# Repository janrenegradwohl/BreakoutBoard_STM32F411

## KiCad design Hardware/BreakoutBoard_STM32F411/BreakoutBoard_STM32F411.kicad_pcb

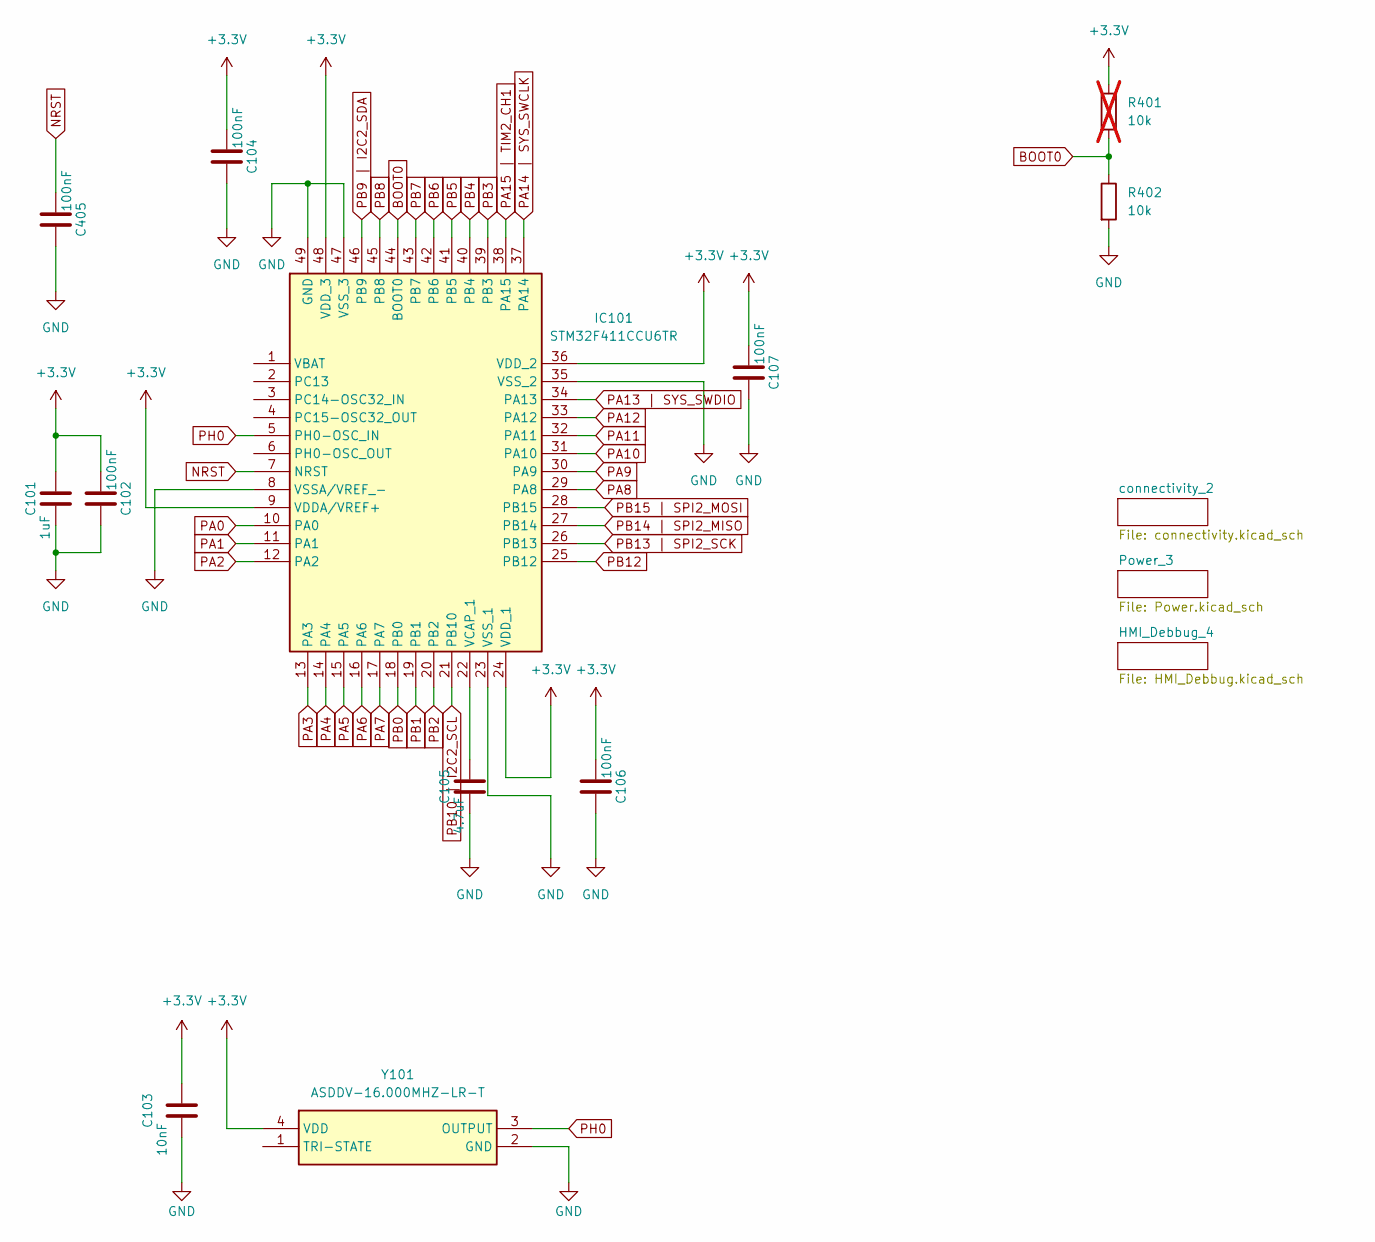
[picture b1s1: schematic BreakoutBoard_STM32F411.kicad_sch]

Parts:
C101: 1uF; C_0603_1608Metric
C102, C104, C106, C107, C405: 100nF; C_0402_1005Metric
C103: 10nF; C_0402_1005Metric
C105: 4.7uF; C_0805_2012Metric
IC101: STM32F411CCU6TR; QFN50P700X700X65-49N-D; Mouser Part Number 511-STM32F411CCU6TR
R401: 10k; R_0402_1005Metric; not fitted
R402: 10k; R_0402_1005Metric
Y101: ASDDV-16.000MHZ-LR-T; AbraconASDDV; Mouser Part Number 815-ASDDV-1600MHZLRT

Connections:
+3.3V: C101.2, C102.1, C103.2, C104.1, C106.1, C107.1, IC101.9 (VDDA/VREF+), IC101.24 (VDD_1), IC101.36 (VDD_2), IC101.48 (VDD_3), R401.1, Y101.4 (VDD); also elsewhere on the board
BOOT0: IC101.44 (BOOT0), R401.2, R402.1
GND: C101.1, C102.2, C103.1, C104.2, C105.1, C106.2, C107.2, C405.2, IC101.8 (VSSA/VREF_-), IC101.23 (VSS_1), IC101.35 (VSS_2), IC101.47 (VSS_3), IC101.49 (GND), R402.2, Y101.2 (GND); also elsewhere on the board
NRST: C405.1, IC101.7 (NRST)
unnamed: C105.2, IC101.22 (VCAP_1)
PA0: IC101.10 (PA0); also elsewhere on the board
PA1: IC101.11 (PA1); also elsewhere on the board
PA2: IC101.12 (PA2); also elsewhere on the board
PA3: IC101.13 (PA3); also elsewhere on the board
PA4: IC101.14 (PA4); also elsewhere on the board
PA5: IC101.15 (PA5); also elsewhere on the board
PA6: IC101.16 (PA6); also elsewhere on the board
PA7: IC101.17 (PA7); also elsewhere on the board
PA8: IC101.29 (PA8); also elsewhere on the board
PA9: IC101.30 (PA9); also elsewhere on the board
PA10: IC101.31 (PA10); also elsewhere on the board
PA11: IC101.32 (PA11); also elsewhere on the board
PA12: IC101.33 (PA12); also elsewhere on the board
PA13 | SYS_SWDIO: IC101.34 (PA13); also elsewhere on the board
PA14 | SYS_SWCLK: IC101.37 (PA14); also elsewhere on the board
PA15 | TIM2_CH1: IC101.38 (PA15); also elsewhere on the board
PB0: IC101.18 (PB0); also elsewhere on the board
PB1: IC101.19 (PB1); also elsewhere on the board
PB2: IC101.20 (PB2)
PB3: IC101.39 (PB3); also elsewhere on the board
PB4: IC101.40 (PB4); also elsewhere on the board
PB5: IC101.41 (PB5); also elsewhere on the board
PB6: IC101.42 (PB6); also elsewhere on the board
PB7: IC101.43 (PB7); also elsewhere on the board
PB8: IC101.45 (PB8); also elsewhere on the board
PB9 | I2C2_SDA: IC101.46 (PB9)
PB10 | I2C2_SCL: IC101.21 (PB10)
PB12: IC101.25 (PB12); also elsewhere on the board
PB13 | SPI2_SCK: IC101.26 (PB13); also elsewhere on the board
PB14 | SPI2_MISO: IC101.27 (PB14); also elsewhere on the board
PB15 | SPI2_MOSI: IC101.28 (PB15); also elsewhere on the board
PH0: IC101.5 (PH0-OSC_IN), Y101.3 (OUTPUT)

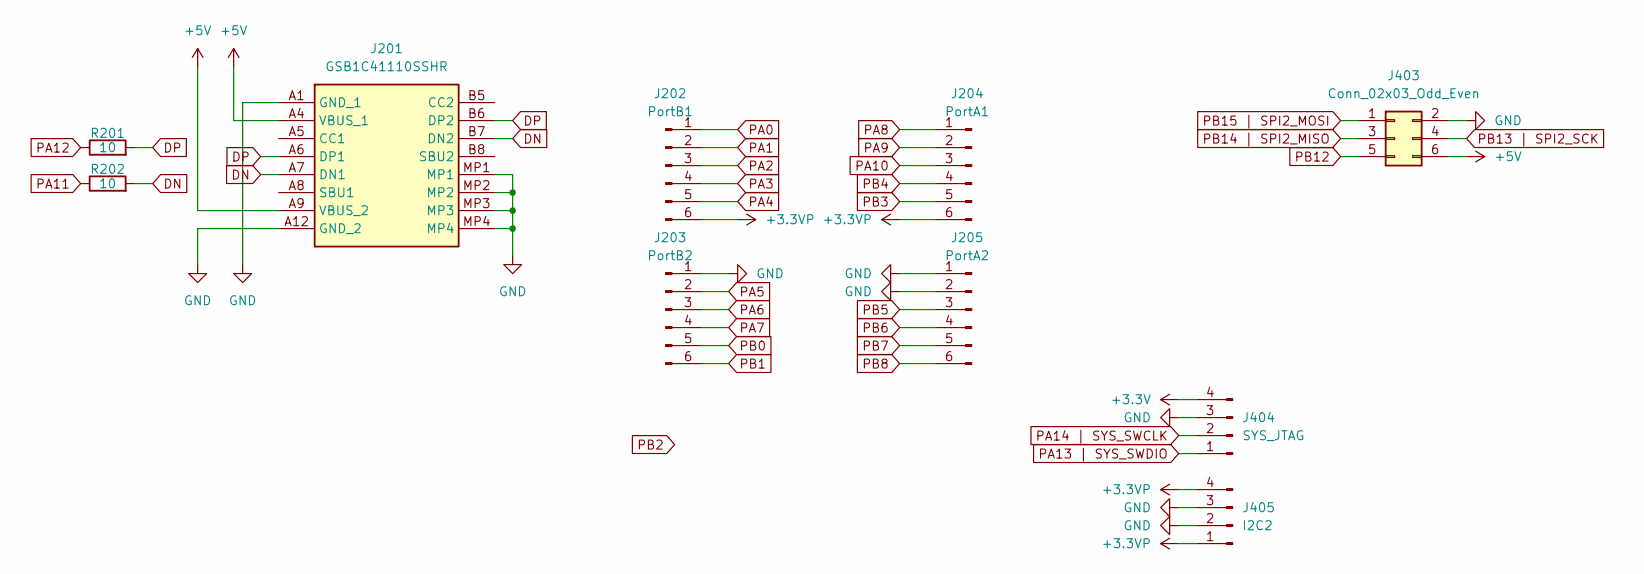
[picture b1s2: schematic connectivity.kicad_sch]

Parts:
J201: GSB1C41110SSHR; Manufacturer_Part_Number GSB1C41110SSHR
J202: PortB1; PinHeader_1x06_P2.54mm_Vertical
J203: PortB2; PinHeader_1x06_P2.54mm_Vertical
J204: PortA1; PinHeader_1x06_P2.54mm_Vertical
J205: PortA2; PinHeader_1x06_P2.54mm_Vertical
J403: Conn_02x03_Odd_Even; PinHeader_2x03_P2.54mm_Vertical
J404: SYS_JTAG; PinHeader_1x04_P2.54mm_Vertical
J405: I2C2; PinHeader_1x04_P2.54mm_Vertical
R201, R202: 10; R_0603_1608Metric

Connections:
+3.3V: J404.4; also elsewhere on the board
+3.3VP: J202.6, J204.6, J405.1, J405.4; also elsewhere on the board
+5V: J201.A4 (VBUS_1), J201.A9 (VBUS_2), J403.6; also elsewhere on the board
DN: J201.A7 (DN1), J201.B7 (DN2), R202.2
DP: J201.A6 (DP1), J201.B6 (DP2), R201.2
GND: J201.A1 (GND_1), J201.A12 (GND_2), J201.MP1, J201.MP2, J201.MP3, J201.MP4, J203.1, J205.1, J205.2, J403.2, J404.3, J405.2, J405.3; also elsewhere on the board
PA0: J202.1; also elsewhere on the board
PA1: J202.2; also elsewhere on the board
PA2: J202.3; also elsewhere on the board
PA3: J202.4; also elsewhere on the board
PA4: J202.5; also elsewhere on the board
PA5: J203.2; also elsewhere on the board
PA6: J203.3; also elsewhere on the board
PA7: J203.4; also elsewhere on the board
PA8: J204.1; also elsewhere on the board
PA9: J204.2; also elsewhere on the board
PA10: J204.3; also elsewhere on the board
PA11: R202.1; also elsewhere on the board
PA12: R201.1; also elsewhere on the board
PA13 | SYS_SWDIO: J404.1; also elsewhere on the board
PA14 | SYS_SWCLK: J404.2; also elsewhere on the board
PB0: J203.5; also elsewhere on the board
PB1: J203.6; also elsewhere on the board
PB3: J204.5; also elsewhere on the board
PB4: J204.4; also elsewhere on the board
PB5: J205.3; also elsewhere on the board
PB6: J205.4; also elsewhere on the board
PB7: J205.5; also elsewhere on the board
PB8: J205.6; also elsewhere on the board
PB12: J403.5; also elsewhere on the board
PB13 | SPI2_SCK: J403.4; also elsewhere on the board
PB14 | SPI2_MISO: J403.3; also elsewhere on the board
PB15 | SPI2_MOSI: J403.1; also elsewhere on the board

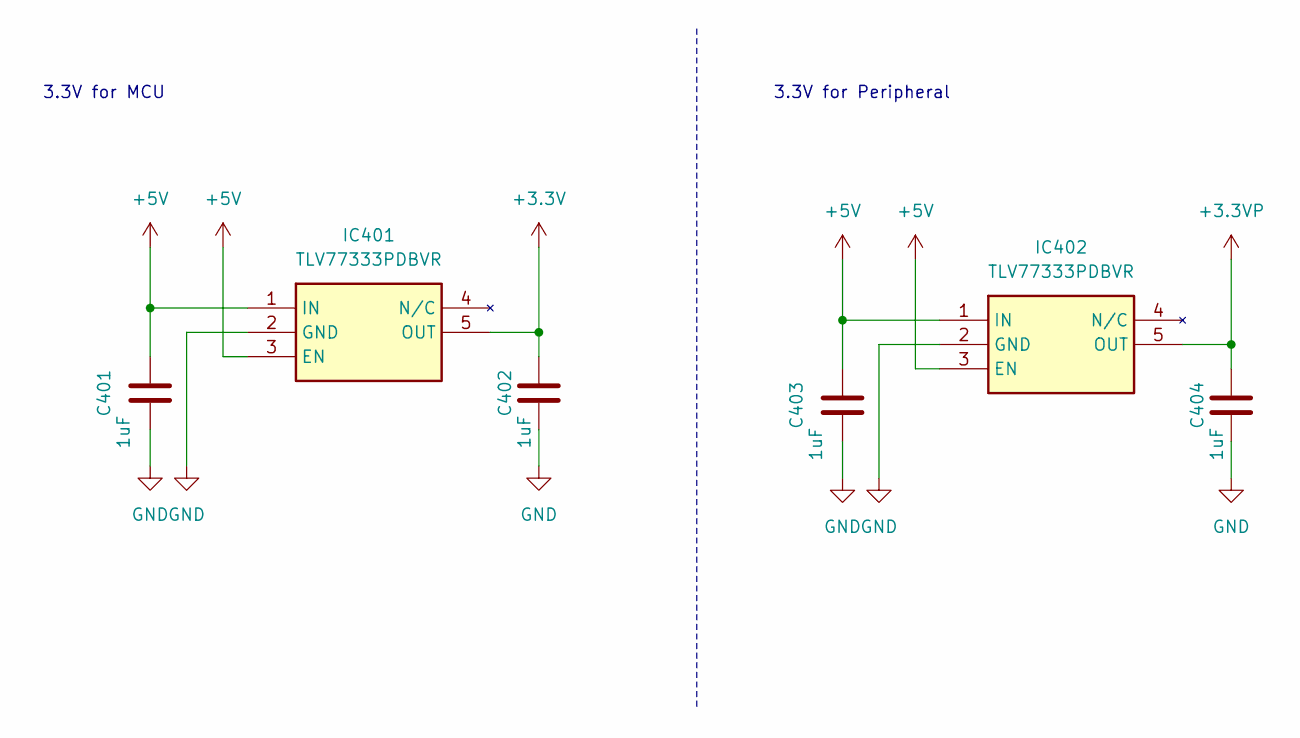
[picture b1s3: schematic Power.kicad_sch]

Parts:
C401, C402, C403, C404: 1uF; C_0603_1608Metric
IC401, IC402: TLV77333PDBVR; SOT95P280X145-5N; Mouser Part Number 595-TLV77333PDBVR

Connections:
+3.3V: C402.2, IC401.5 (OUT); also elsewhere on the board
+3.3VP: C404.2, IC402.5 (OUT); also elsewhere on the board
+5V: C401.2, C403.2, IC401.1 (IN), IC401.3 (EN), IC402.1 (IN), IC402.3 (EN); also elsewhere on the board
GND: C401.1, C402.1, C403.1, C404.1, IC401.2 (GND), IC402.2 (GND); also elsewhere on the board

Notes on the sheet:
3.3V for MCU
3.3V for Peripheral

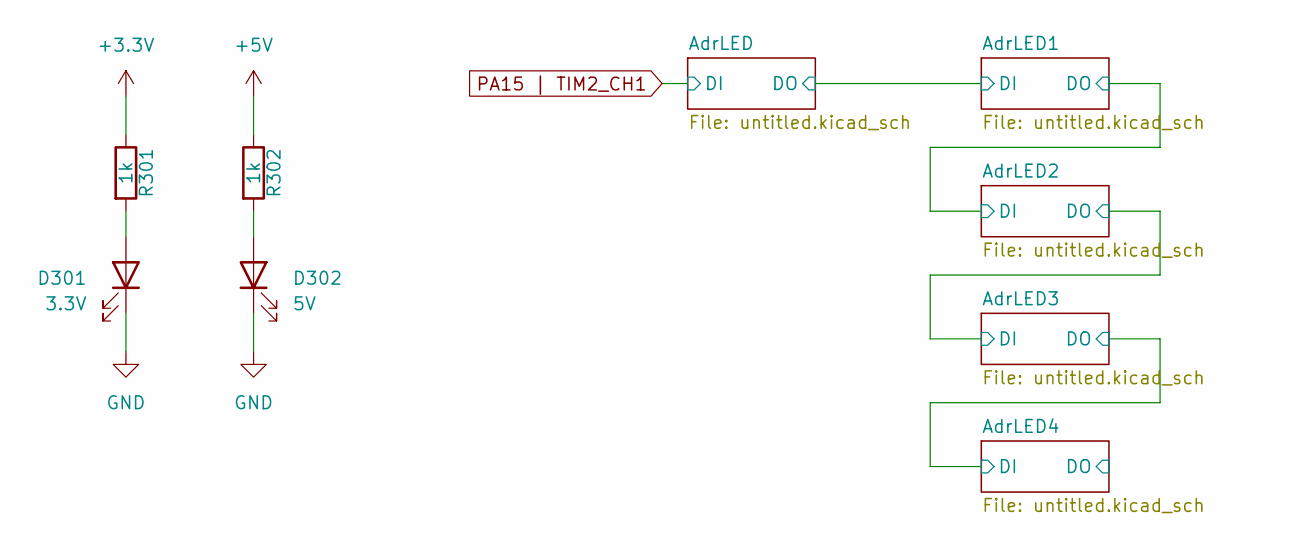
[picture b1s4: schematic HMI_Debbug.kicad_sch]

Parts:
D301: 3.3V; LED_0603_1608Metric
D302: 5V; LED_0603_1608Metric
R301, R302: 1k; R_0603_1608Metric

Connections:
+3.3V: R301.1; also elsewhere on the board
+5V: R302.1; also elsewhere on the board
GND: D301.1 (K), D302.1 (K); also elsewhere on the board
unnamed: D301.2 (A), R301.2
unnamed: D302.2 (A), R302.2

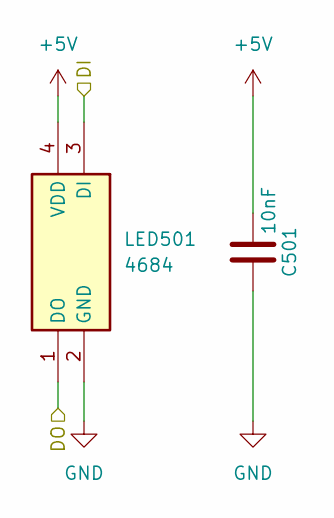
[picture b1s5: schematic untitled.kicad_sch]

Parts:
C501: 10nF; C_0402_1005Metric
LED501: 4684; Mouser Part Number 485-4684

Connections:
+5V: C501.1, LED501.4 (VDD); also elsewhere on the board
/HMI_Debbug_4/AdrLED/DO: LED501.1 (DO); also elsewhere on the board
GND: C501.2, LED501.2 (GND); also elsewhere on the board
PA15 | TIM2_CH1: LED501.3 (DI); also elsewhere on the board

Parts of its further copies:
C601, C701, C801, C901: 10nF; C_0402_1005Metric
LED601, LED701, LED801, LED901: 4684; Mouser Part Number 485-4684

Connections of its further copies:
+5V: C601.1, C701.1, C801.1, C901.1, LED601.4 (VDD), LED701.4 (VDD), LED801.4 (VDD), LED901.4 (VDD); also elsewhere on the board
/HMI_Debbug_4/AdrLED1/DO: LED601.1 (DO), LED701.3 (DI)
/HMI_Debbug_4/AdrLED2/DO: LED701.1 (DO), LED801.3 (DI)
/HMI_Debbug_4/AdrLED3/DO: LED801.1 (DO), LED901.3 (DI)
/HMI_Debbug_4/AdrLED4/DO: LED901.1 (DO)
/HMI_Debbug_4/AdrLED/DO: LED601.3 (DI); also elsewhere on the board
GND: C601.2, C701.2, C801.2, C901.2, LED601.2 (GND), LED701.2 (GND), LED801.2 (GND), LED901.2 (GND); also elsewhere on the board

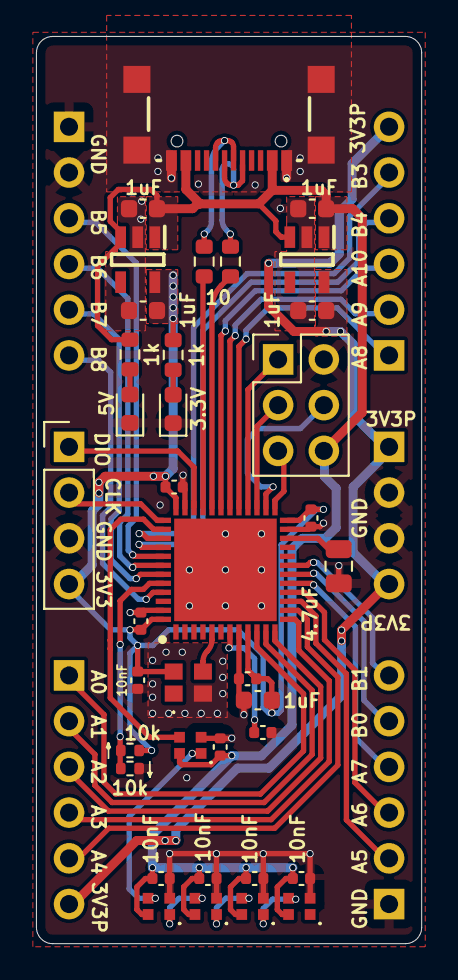
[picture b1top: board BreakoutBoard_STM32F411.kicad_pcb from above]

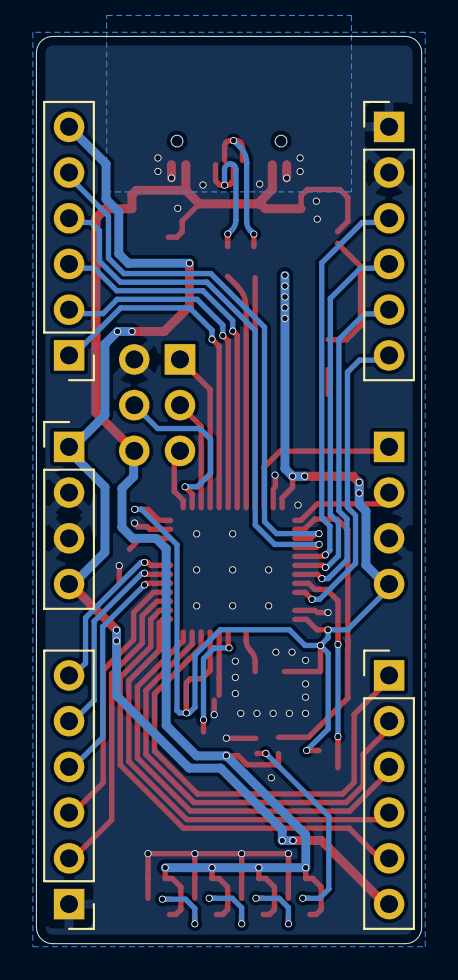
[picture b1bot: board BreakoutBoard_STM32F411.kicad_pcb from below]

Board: 4 copper layers, 21.4 x 50.4 mm, 42 parts (5 on the bottom side), 44 nets.

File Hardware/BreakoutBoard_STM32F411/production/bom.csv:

Designator,Footprint,Quantity,Value,LCSC Part #
"C101, C401, C402, C403, C404",0603,5,1uF,
"C102, C104, C106, C107, C405",0402,5,100nF,
"C103, C501, C601, C701, C801, C901",0402,6,10nF,
C105,0805,1,4.7uF,
D301,0603,1,3.3V,
D302,0603,1,5V,
IC101,QFN50P700X700X65-49N-D,1,STM32F411CCU6TR,
"IC401, IC402",SOT95P280X145-5N,2,TLV77333PDBVR,
J201,GSB1C41110SSHR,1,GSB1C41110SSHR,
J202,PinHeader_1x06_P2.54mm_Vertical,1,PortB1,
J203,PinHeader_1x06_P2.54mm_Vertical,1,PortB2,
J204,PinHeader_1x06_P2.54mm_Vertical,1,PortA1,
J205,PinHeader_1x06_P2.54mm_Vertical,1,PortA2,
J403,PinHeader_2x03_P2.54mm_Vertical,1,Conn_02x03_Odd_Even,
J404,PinHeader_1x04_P2.54mm_Vertical,1,SYS_JTAG,
J405,PinHeader_1x04_P2.54mm_Vertical,1,I2C2,
"LED501, LED601, LED701, LED801, LED901",4684,5,4684,
"R201, R202",0603,2,10,
"R301, R302",0603,2,1k,
R402,0402,1,10k,
Y101,AbraconASDDV,1,ASDDV-16.000MHZ-LR-T,

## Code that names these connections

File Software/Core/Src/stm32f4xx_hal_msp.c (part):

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
    __HAL_RCC_GPIOB_CLK_ENABLE();
    /**SPI2 GPIO Configuration
    PB13     ------> SPI2_SCK
    PB14     ------> SPI2_MISO
    PB15     ------> SPI2_MOSI
    */
    GPIO_InitStruct.Pin = GPIO_PIN_13|GPIO_PIN_14|GPIO_PIN_15;
    GPIO_InitStruct.Mode = GPIO_MODE_AF_PP;
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    __HAL_RCC_SPI2_CLK_DISABLE();

    /**SPI2 GPIO Configuration
    PB13     ------> SPI2_SCK
    PB14     ------> SPI2_MISO
    PB15     ------> SPI2_MOSI
    */
    HAL_GPIO_DeInit(GPIOB, GPIO_PIN_13|GPIO_PIN_14|GPIO_PIN_15);

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
    __HAL_RCC_GPIOA_CLK_ENABLE();
    /**TIM2 GPIO Configuration
    PA15     ------> TIM2_CH1
    */
    GPIO_InitStruct.Pin = GPIO_PIN_15;
    GPIO_InitStruct.Mode = GPIO_MODE_AF_PP;
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
    __HAL_RCC_GPIOA_CLK_ENABLE();
    /**USB_OTG_FS GPIO Configuration
    PA11     ------> USB_OTG_FS_DM
    PA12     ------> USB_OTG_FS_DP
    */
    GPIO_InitStruct.Pin = GPIO_PIN_11|GPIO_PIN_12;
    GPIO_InitStruct.Mode = GPIO_MODE_AF_PP;
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    __HAL_RCC_USB_OTG_FS_CLK_DISABLE();

    /**USB_OTG_FS GPIO Configuration
    PA11     ------> USB_OTG_FS_DM
    PA12     ------> USB_OTG_FS_DP
    */
    HAL_GPIO_DeInit(GPIOA, GPIO_PIN_11|GPIO_PIN_12);

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
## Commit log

2026-04-05 Initial Push
2026-04-05 added:components
2026-04-05 added:components (#1)
2026-04-05 edited: default design rules
2026-04-05 edited: default design rules (#2)
2026-04-05 arranged:components
2026-04-05 arranged:components (#3)
2026-04-06 routed PCB
2026-04-06 routed PCB (#4)
2026-04-08 fixed:Viasize, fixed:NRST and BOOT0
2026-04-08 fixed:Viasize, fixed:NRST and BOOT0 (#5)
2026-04-09 fixed:Via size, fixed:DRC, edited:Silkscreen
2026-04-09 fixed:Via size, fixed:DRC, edited:Silkscreen (#6)
2026-04-09 added:labeling, changed:5V to 3V3P
2026-04-09 added:labeling, changed:5V to 3V3P (#7)
2026-04-09 fixed:edgecut, checked:pinheader spacing
2026-04-09 fixed:edgecut, checked:pinheader spacing (#8)
2026-04-14 ordering Version
2026-04-15 ordering Version (#9)
2026-05-08 feat: created WS2812B.c file (#10)
2026-05-08 feat: created WS2812B.c file
2026-05-11 feat: init tim1
2026-05-11 feat: init tim1 (#11)
2026-05-11 feat:TIM2 PWM DMA
2026-05-11 added:Neopixel
2026-05-18 feat: one adres.LED works

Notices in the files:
Software/Core/Src/stm32f4xx_hal_msp.c:
Copyright (c) 2026 STMicroelectronics.
All rights reserved.
This software is licensed under terms that can be found in the LICENSE file
